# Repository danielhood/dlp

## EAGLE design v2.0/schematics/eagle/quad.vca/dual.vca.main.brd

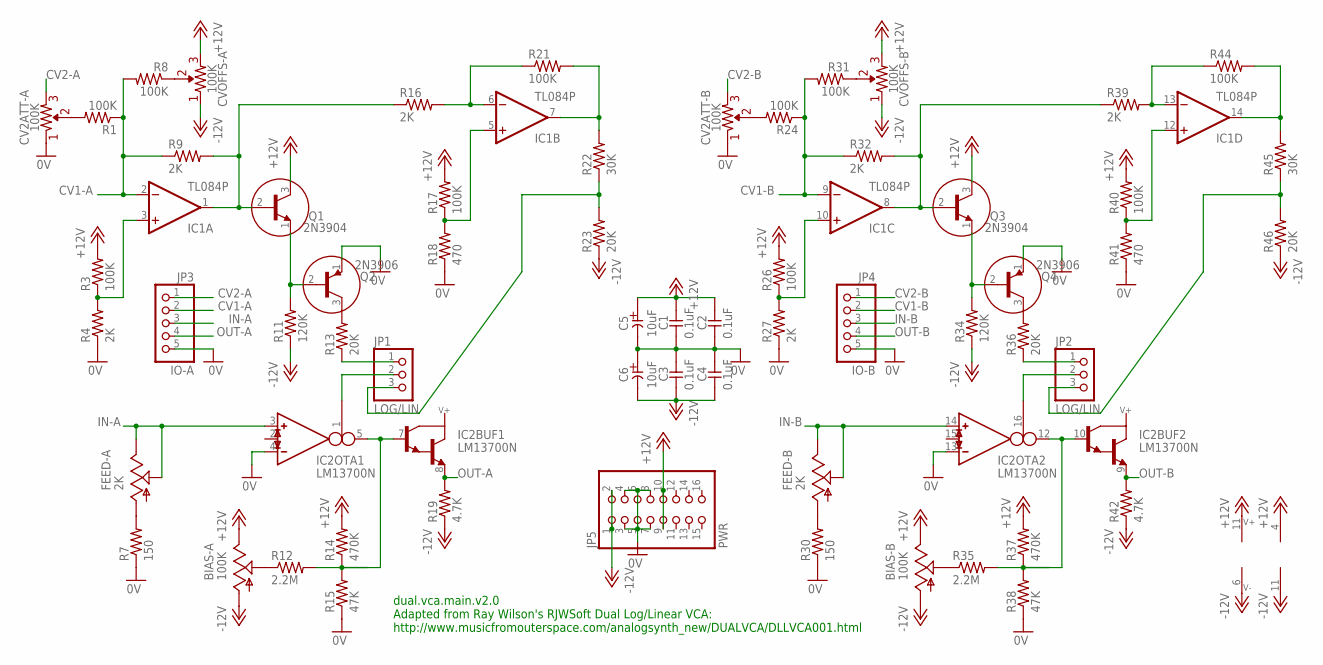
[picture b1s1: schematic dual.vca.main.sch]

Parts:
BIAS-A: 100K; PT-10S
BIAS-B: 100K; PT-10S
C1, C2, C3, C4: 0.1uF; C025-024X044
C5, C6: 10uF; E2-5
CV2ATT-A, CV2ATT-B: 100K; R-VAR
CVOFFS-A: 100K; R-VAR
CVOFFS-B: 100K; R-VAR
FEED-A: 2K; PT-10S
FEED-B: 2K; PT-10S
IC1: TL084P; DIL14
IC2: LM13700N; DIL16
JP1, JP2: LOG/LIN; 1X03
JP3: IO-A; 1X05
JP4: IO-B; 1X05
JP5: PWR; 2X08
Q1, Q3: 2N3904; TO92
Q2, Q4: 2N3906; TO92
R1, R3, R8, R17, R21, R24, R26, R31, R40, R44: 100K; 0207/7
R4, R9, R16, R27, R32, R39: 2K; 0207/7
R7, R30: 150; 0207/7
R11, R34: 120K; 0207/7
R12, R35: 2.2M; 0207/7
R13, R23, R36, R46: 20K; 0207/7
R14, R37: 470K; 0207/7
R15, R38: 47K; 0207/7
R18, R41: 470; 0207/7
R19, R42: 4.7K; 0207/7
R22, R45: 30K; 0207/7

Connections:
0V: C1.2, C2.2, C3.1, C4.1, C5.-, C6.+, CV2ATT-A.R1 (1), CV2ATT-B.R1 (1), IC2.4 (IN_N), IC2.13 (IN_N), JP3.5, JP4.5, JP5.3, JP5.4, JP5.5, JP5.6, JP5.7, JP5.8, Q2.1 (E), Q4.1 (E), R4.1, R7.1, R15.1, R18.1, R27.1, R30.1, R38.1, R41.1
+12V: BIAS-A.E, BIAS-B.E, C1.1, C2.1, C5.+, CVOFFS-A.R2 (2), CVOFFS-B.R2 (2), IC1.4 (V+), IC2.11 (V+), JP5.9, JP5.10, Q1.3 (C), Q3.3 (C), R3.2, R14.2, R17.2, R26.2, R37.2, R40.2
-12V: BIAS-A.A, BIAS-B.A, C3.2, C4.2, C6.-, CVOFFS-A.R1 (1), CVOFFS-B.R1 (1), IC1.11 (V-), IC2.6 (V-), JP5.1, JP5.2, R11.1, R19.1, R23.1, R34.1, R42.1, R46.1
CV1-A: IC1.2 (-IN), JP3.2, R1.1, R8.2, R9.1
CV1-B: IC1.9 (-IN), JP4.2, R24.1, R31.2, R32.1
CV2-A: CV2ATT-A.R2 (2), JP3.1
CV2-B: CV2ATT-B.R2 (2), JP4.1
IN-A: FEED-A.E, FEED-A.S, IC2.3 (IN_P), JP3.3
IN-B: FEED-B.E, FEED-B.S, IC2.14 (IN_P), JP4.3
unnamed: Q2.3 (C), R13.2
unnamed: Q4.3 (C), R36.2
unnamed: IC1.3 (+IN), R3.1, R4.2
unnamed: CVOFFS-A.VAR, R8.1
unnamed: IC1.1 (OUT), Q1.2 (B), R9.2, R16.1
unnamed: Q1.1 (E), Q2.2 (B), R11.2
unnamed: FEED-A.A, R7.2
unnamed: JP1.1, R13.1
unnamed: BIAS-A.S, R12.1
unnamed: IC2.5 (OUT), IC2.7 (B), R12.2, R14.1, R15.2
unnamed: CV2ATT-A.VAR, R1.2
unnamed: JP1.3, R22.1, R23.2
unnamed: IC1.5 (+IN), R17.1, R18.2
unnamed: IC1.6 (-IN), R16.2, R21.1
unnamed: IC2.1 (I_BIAS), JP1.2
unnamed: IC1.7 (OUT), R21.2, R22.2
unnamed: IC1.10 (+IN), R26.1, R27.2
unnamed: CVOFFS-B.VAR, R31.1
unnamed: IC1.8 (OUT), Q3.2 (B), R32.2, R39.1
unnamed: Q3.1 (E), Q4.2 (B), R34.2
unnamed: FEED-B.A, R30.2
unnamed: BIAS-B.S, R35.1
unnamed: IC2.10 (B), IC2.12 (OUT), R35.2, R37.1, R38.2
unnamed: CV2ATT-B.VAR, R24.2
unnamed: IC1.12 (+IN), R40.1, R41.2
unnamed: IC1.13 (-IN), R39.2, R44.1
unnamed: IC1.14 (OUT), R44.2, R45.2
unnamed: JP2.1, R36.1
unnamed: JP2.3, R45.1, R46.2
unnamed: IC2.16 (I_BIAS), JP2.2
OUT-A: IC2.8 (E), JP3.4, R19.2
OUT-B: IC2.9 (E), JP4.4, R42.2

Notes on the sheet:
dual.vca.main.v2.0 Adapted from Ray Wilson's RJWSoft Dual Log/Linear VCA: http://www.musicfromouterspace.com/analogsynth_new/DUALVCA/DLLVCA001.html

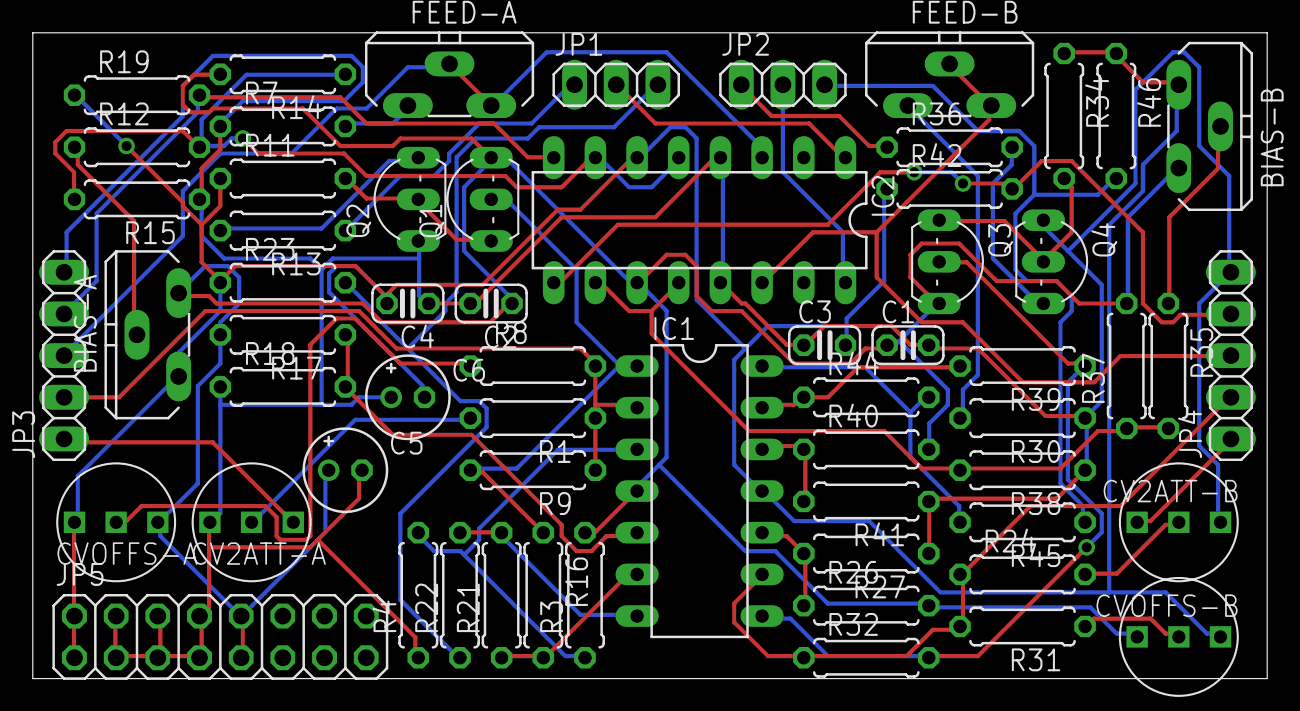
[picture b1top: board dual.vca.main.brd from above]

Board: 2 copper layers, 75.2 x 39.4 mm, 61 parts (0 on the bottom side), 41 nets.

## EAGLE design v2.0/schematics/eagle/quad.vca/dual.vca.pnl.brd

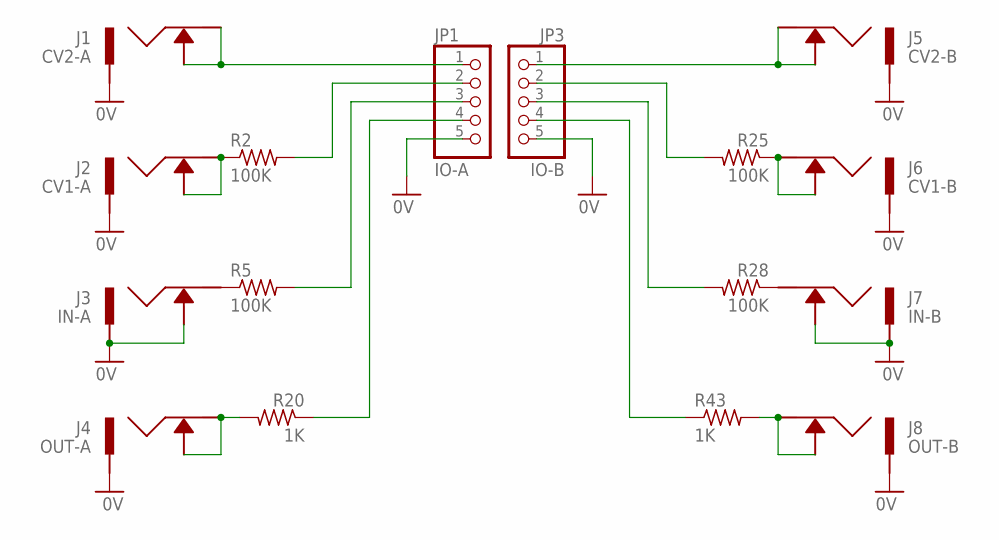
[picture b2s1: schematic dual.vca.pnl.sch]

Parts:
J1: CV2-A; ACJM-MV35-2S
J2: CV1-A; ACJM-MV35-2S
J3: IN-A; ACJM-MV35-2S
J4: OUT-A; ACJM-MV35-2S
J5: CV2-B; ACJM-MV35-2S
J6: CV1-B; ACJM-MV35-2S
J7: IN-B; ACJM-MV35-2S
J8: OUT-B; ACJM-MV35-2S
JP1: IO-A; 1X05
JP3: IO-B; 1X05
R2, R5, R25, R28: 100K; 0207/7
R20, R43: 1K; 0207/7

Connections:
0V: J1.P$1, J2.P$1, J3.P$1, J3.P$2, J4.P$1, J5.P$1, J6.P$1, J7.P$1, J7.P$2, J8.P$1, JP1.5, JP3.5
unnamed: J2.P$2, J2.P$3, R2.1
unnamed: J4.P$2, J4.P$3, R20.2
unnamed: JP1.2, R2.2
unnamed: JP1.3, R5.2
unnamed: JP1.4, R20.1
unnamed: JP3.2, R25.2
unnamed: JP3.3, R28.2
unnamed: JP3.4, R43.1
unnamed: J3.P$3, R5.1
unnamed: J1.P$2, J1.P$3, JP1.1
unnamed: J6.P$2, J6.P$3, R25.1
unnamed: J8.P$2, J8.P$3, R43.2
unnamed: J7.P$3, R28.1
unnamed: J5.P$2, J5.P$3, JP3.1

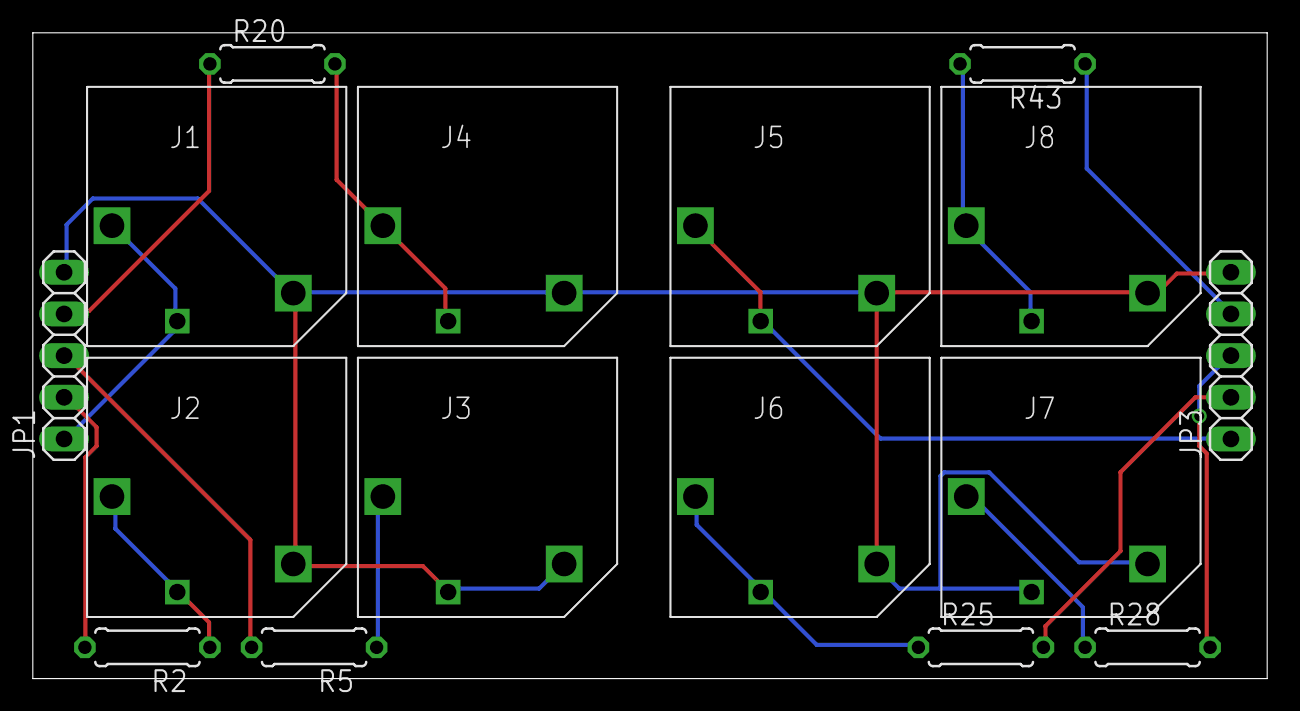
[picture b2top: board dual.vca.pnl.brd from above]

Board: 2 copper layers, 75.2 x 39.4 mm, 16 parts (0 on the bottom side), 15 nets.

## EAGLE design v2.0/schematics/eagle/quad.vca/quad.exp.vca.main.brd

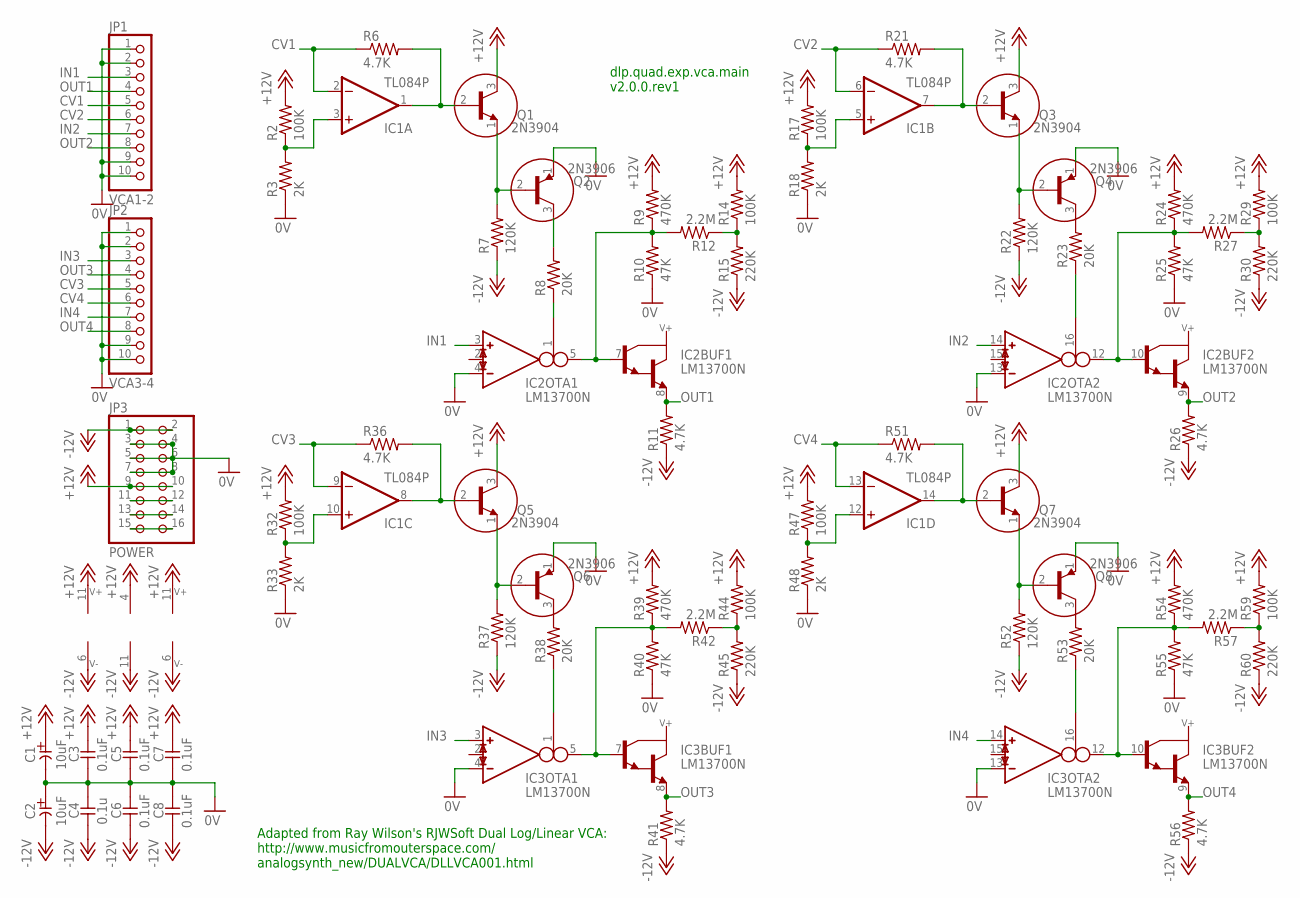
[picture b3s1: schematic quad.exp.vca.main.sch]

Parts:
C1, C2: 10uF; E2-5
C3, C5, C6, C7, C8: 0.1uF; C025-024X044
C4: 0.1u; C025-024X044
IC1: TL084P; DIL14
IC2, IC3: LM13700N; DIL16
JP1: VCA1-2; 1X10
JP2: VCA3-4; 1X10
JP3: POWER; 2X08
Q1, Q3, Q5, Q7: 2N3904; TO92
Q2, Q4, Q6, Q8: 2N3906; TO92
R2, R14, R17, R29, R32, R44, R47, R59: 100K; 0207/7
R3, R18, R33, R48: 2K; 0207/7
R6, R11, R21, R26, R36, R41, R51, R56: 4.7K; 0207/7
R7, R22, R37, R52: 120K; 0207/7
R8, R23, R38, R53: 20K; 0207/7
R9, R24, R39, R54: 470K; 0207/7
R10, R25, R40, R55: 47K; 0207/7
R12, R27, R42, R57: 2.2M; 0207/7
R15, R30, R45, R60: 220K; 0207/7

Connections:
0V: C1.-, C2.+, C3.2, C4.1, C5.2, C6.1, C7.2, C8.1, IC2.4 (IN_N), IC2.13 (IN_N), IC3.4 (IN_N), IC3.13 (IN_N), JP1.1, JP1.2, JP1.9, JP1.10, JP2.1, JP2.2, JP2.9, JP2.10, JP3.3, JP3.4, JP3.5, JP3.6, JP3.7, JP3.8, Q2.1 (E), Q4.1 (E), Q6.1 (E), Q8.1 (E), R3.1, R10.1, R18.1, R25.1, R33.1, R40.1, R48.1, R55.1
+12V: C1.+, C3.1, C5.1, C7.1, IC1.4 (V+), IC2.11 (V+), IC3.11 (V+), JP3.9, JP3.10, Q1.3 (C), Q3.3 (C), Q5.3 (C), Q7.3 (C), R2.2, R9.2, R14.2, R17.2, R24.2, R29.2, R32.2, R39.2, R44.2, R47.2, R54.2, R59.2
-12V: C2.-, C4.2, C6.2, C8.2, IC1.11 (V-), IC2.6 (V-), IC3.6 (V-), JP3.1, JP3.2, R7.1, R11.1, R15.1, R22.1, R26.1, R30.1, R37.1, R41.1, R45.1, R52.1, R56.1, R60.1
CV1: IC1.2 (-IN), JP1.5, R6.1
CV2: IC1.6 (-IN), JP1.6, R21.1
CV3: IC1.9 (-IN), JP2.5, R36.1
CV4: IC1.13 (-IN), JP2.6, R51.1
IN1: IC2.3 (IN_P), JP1.3
IN2: IC2.14 (IN_P), JP1.7
IN3: IC3.3 (IN_P), JP2.3
IN4: IC3.14 (IN_P), JP2.7
unnamed: IC1.3 (+IN), R2.1, R3.2
unnamed: IC1.10 (+IN), R32.1, R33.2
unnamed: IC1.1 (OUT), Q1.2 (B), R6.2
unnamed: Q1.1 (E), Q2.2 (B), R7.2
unnamed: Q2.3 (C), R8.2
unnamed: IC1.8 (OUT), Q5.2 (B), R36.2
unnamed: Q5.1 (E), Q6.2 (B), R37.2
unnamed: IC2.5 (OUT), IC2.7 (B), R9.1, R10.2, R12.2
unnamed: Q4.3 (C), R23.2
unnamed: IC3.5 (OUT), IC3.7 (B), R39.1, R40.2, R42.2
unnamed: IC2.1 (I_BIAS), R8.1
unnamed: IC1.5 (+IN), R17.1, R18.2
unnamed: IC3.1 (I_BIAS), R38.1
unnamed: IC1.7 (OUT), Q3.2 (B), R21.2
unnamed: Q3.1 (E), Q4.2 (B), R22.2
unnamed: Q8.3 (C), R53.2
unnamed: IC1.12 (+IN), R47.1, R48.2
unnamed: IC2.10 (B), IC2.12 (OUT), R24.1, R25.2, R27.2
unnamed: IC1.14 (OUT), Q7.2 (B), R51.2
unnamed: Q7.1 (E), Q8.2 (B), R52.2
unnamed: Q6.3 (C), R38.2
unnamed: IC2.16 (I_BIAS), R23.1
unnamed: IC3.10 (B), IC3.12 (OUT), R54.1, R55.2, R57.2
unnamed: IC3.16 (I_BIAS), R53.1
unnamed: R12.1, R14.1, R15.2
unnamed: R27.1, R29.1, R30.2
unnamed: R42.1, R44.1, R45.2
unnamed: R57.1, R59.1, R60.2
unnamed: JP3.11, JP3.12
unnamed: JP3.13, JP3.14
unnamed: JP3.15, JP3.16
OUT1: IC2.8 (E), JP1.4, R11.2
OUT2: IC2.9 (E), JP1.8, R26.2
OUT3: IC3.8 (E), JP2.4, R41.2
OUT4: IC3.9 (E), JP2.8, R56.2

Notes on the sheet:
Adapted from Ray Wilson's RJWSoft Dual Log/Linear VCA: http://www.musicfromouterspace.com/ analogsynth_new/DUALVCA/DLLVCA001.html
dlp.quad.exp.vca.main v2.0.0.rev1

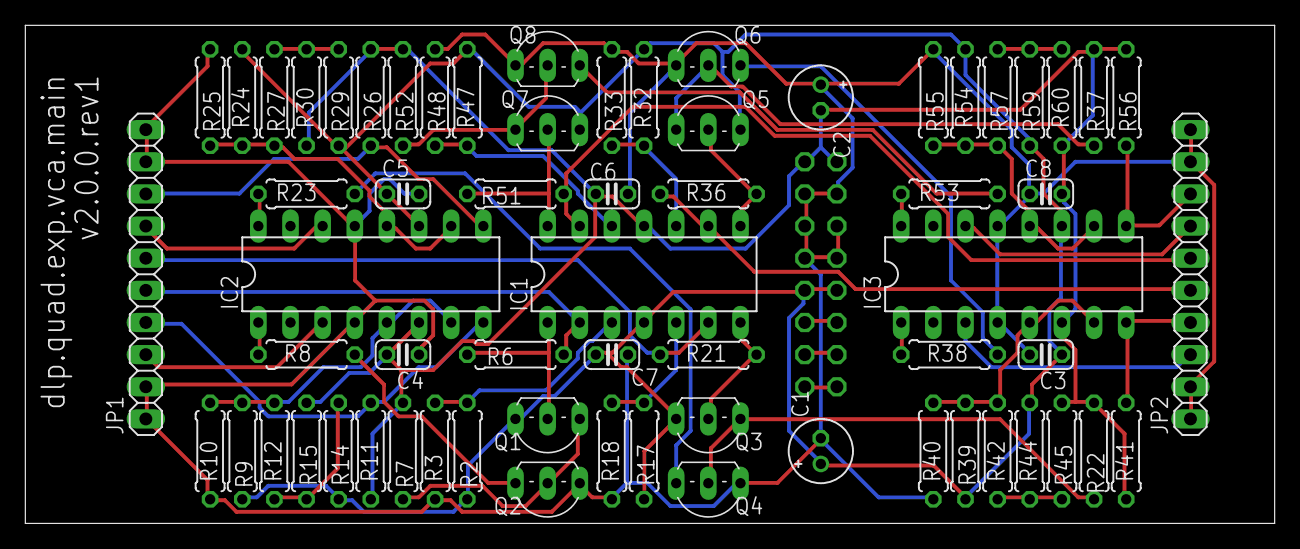
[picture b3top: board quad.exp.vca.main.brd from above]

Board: 2 copper layers, 98.7 x 39.4 mm, 66 parts (1 on the bottom side), 46 nets.

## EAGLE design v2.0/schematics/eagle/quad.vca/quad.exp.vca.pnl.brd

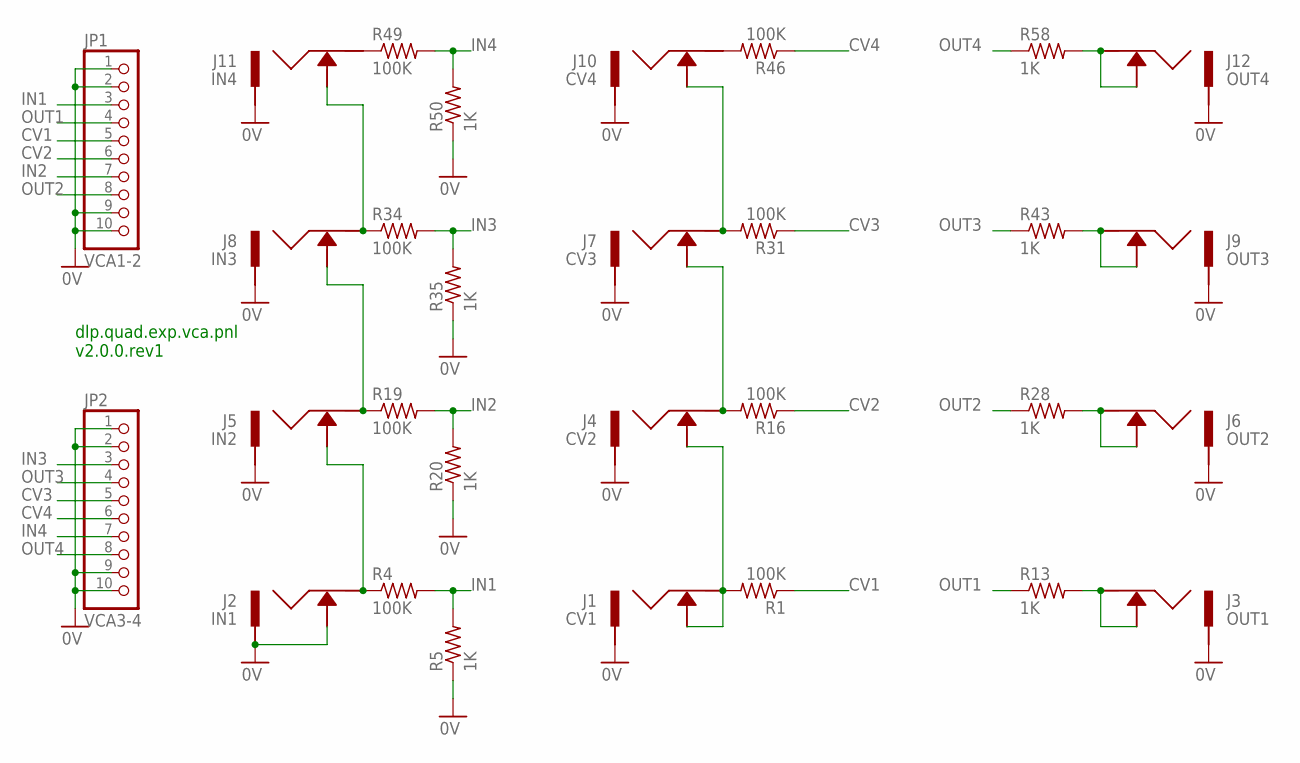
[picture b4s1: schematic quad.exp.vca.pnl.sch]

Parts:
J1: CV1; ACJM-MV35-2S
J2: IN1; ACJM-MV35-2S
J3: OUT1; ACJM-MV35-2S
J4: CV2; ACJM-MV35-2S
J5: IN2; ACJM-MV35-2S
J6: OUT2; ACJM-MV35-2S
J7: CV3; ACJM-MV35-2S
J8: IN3; ACJM-MV35-2S
J9: OUT3; ACJM-MV35-2S
J10: CV4; ACJM-MV35-2S
J11: IN4; ACJM-MV35-2S
J12: OUT4; ACJM-MV35-2S
JP1: VCA1-2; 1X10
JP2: VCA3-4; 1X10
R1, R4, R16, R19, R31, R34, R46, R49: 100K; 0207/7
R5, R13, R20, R28, R35, R43, R50, R58: 1K; 0207/7

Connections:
0V: J1.P$1, J2.P$1, J2.P$2, J3.P$1, J4.P$1, J5.P$1, J6.P$1, J7.P$1, J8.P$1, J9.P$1, J10.P$1, J11.P$1, J12.P$1, JP1.1, JP1.2, JP1.9, JP1.10, JP2.1, JP2.2, JP2.9, JP2.10, R5.1, R20.1, R35.1, R50.1
CV1: JP1.5, R1.1
CV2: JP1.6, R16.1
CV3: JP2.5, R31.1
CV4: JP2.6, R46.1
IN1: JP1.3, R4.2, R5.2
IN2: JP1.7, R19.2, R20.2
IN3: JP2.3, R34.2, R35.2
IN4: JP2.7, R49.2, R50.2
unnamed: J9.P$2, J9.P$3, R43.2
unnamed: J3.P$2, J3.P$3, R13.2
unnamed: J2.P$3, J5.P$2, R4.1
unnamed: J5.P$3, J8.P$2, R19.1
unnamed: J8.P$3, J11.P$2, R34.1
unnamed: J10.P$3, R46.2
unnamed: J7.P$3, J10.P$2, R31.2
unnamed: J4.P$3, J7.P$2, R16.2
unnamed: J1.P$2, J1.P$3, J4.P$2, R1.2
unnamed: J6.P$2, J6.P$3, R28.2
unnamed: J12.P$2, J12.P$3, R58.2
unnamed: J11.P$3, R49.1
OUT1: JP1.4, R13.1
OUT2: JP1.8, R28.1
OUT3: JP2.4, R43.1
OUT4: JP2.8, R58.1

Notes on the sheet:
dlp.quad.exp.vca.pnl v2.0.0.rev1

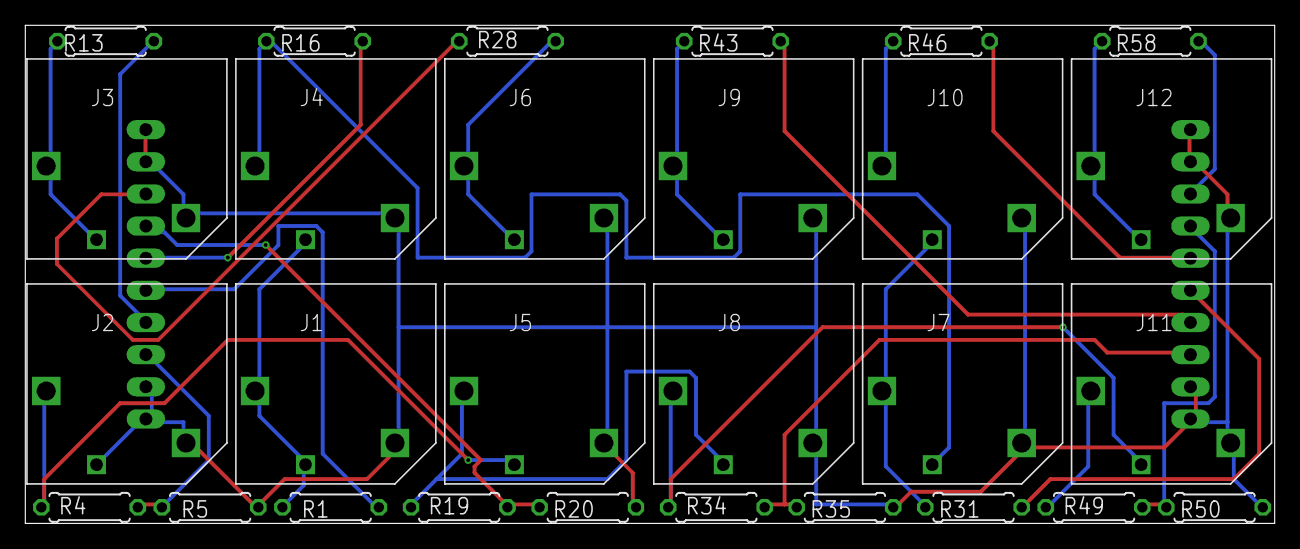
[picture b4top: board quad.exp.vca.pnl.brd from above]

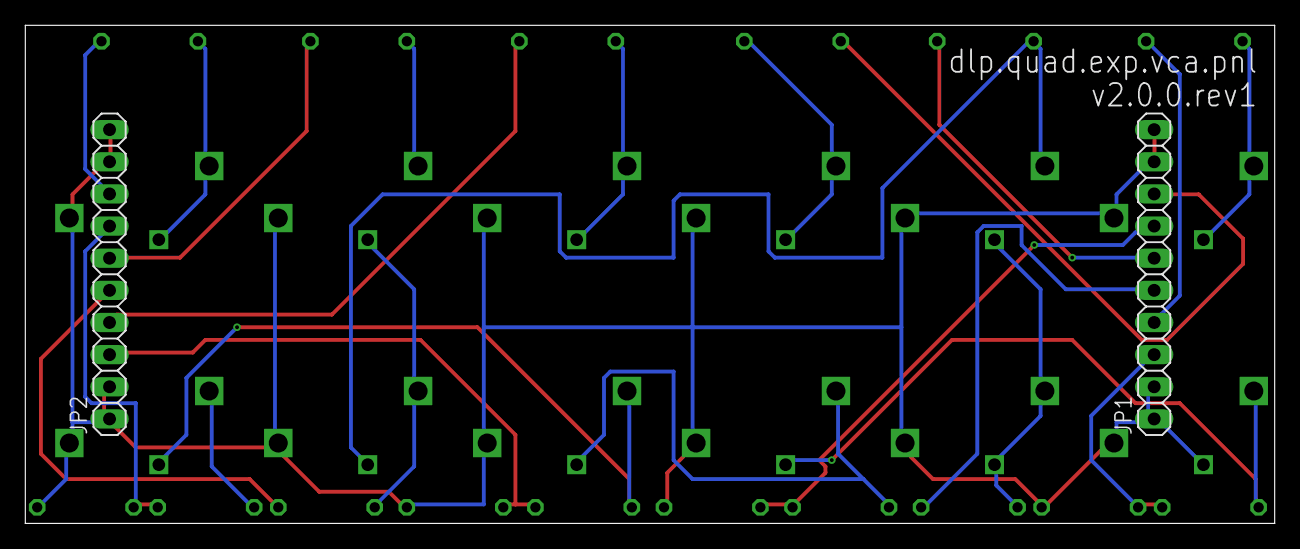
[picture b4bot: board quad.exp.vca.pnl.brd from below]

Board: 2 copper layers, 98.7 x 39.4 mm, 30 parts (2 on the bottom side), 25 nets.

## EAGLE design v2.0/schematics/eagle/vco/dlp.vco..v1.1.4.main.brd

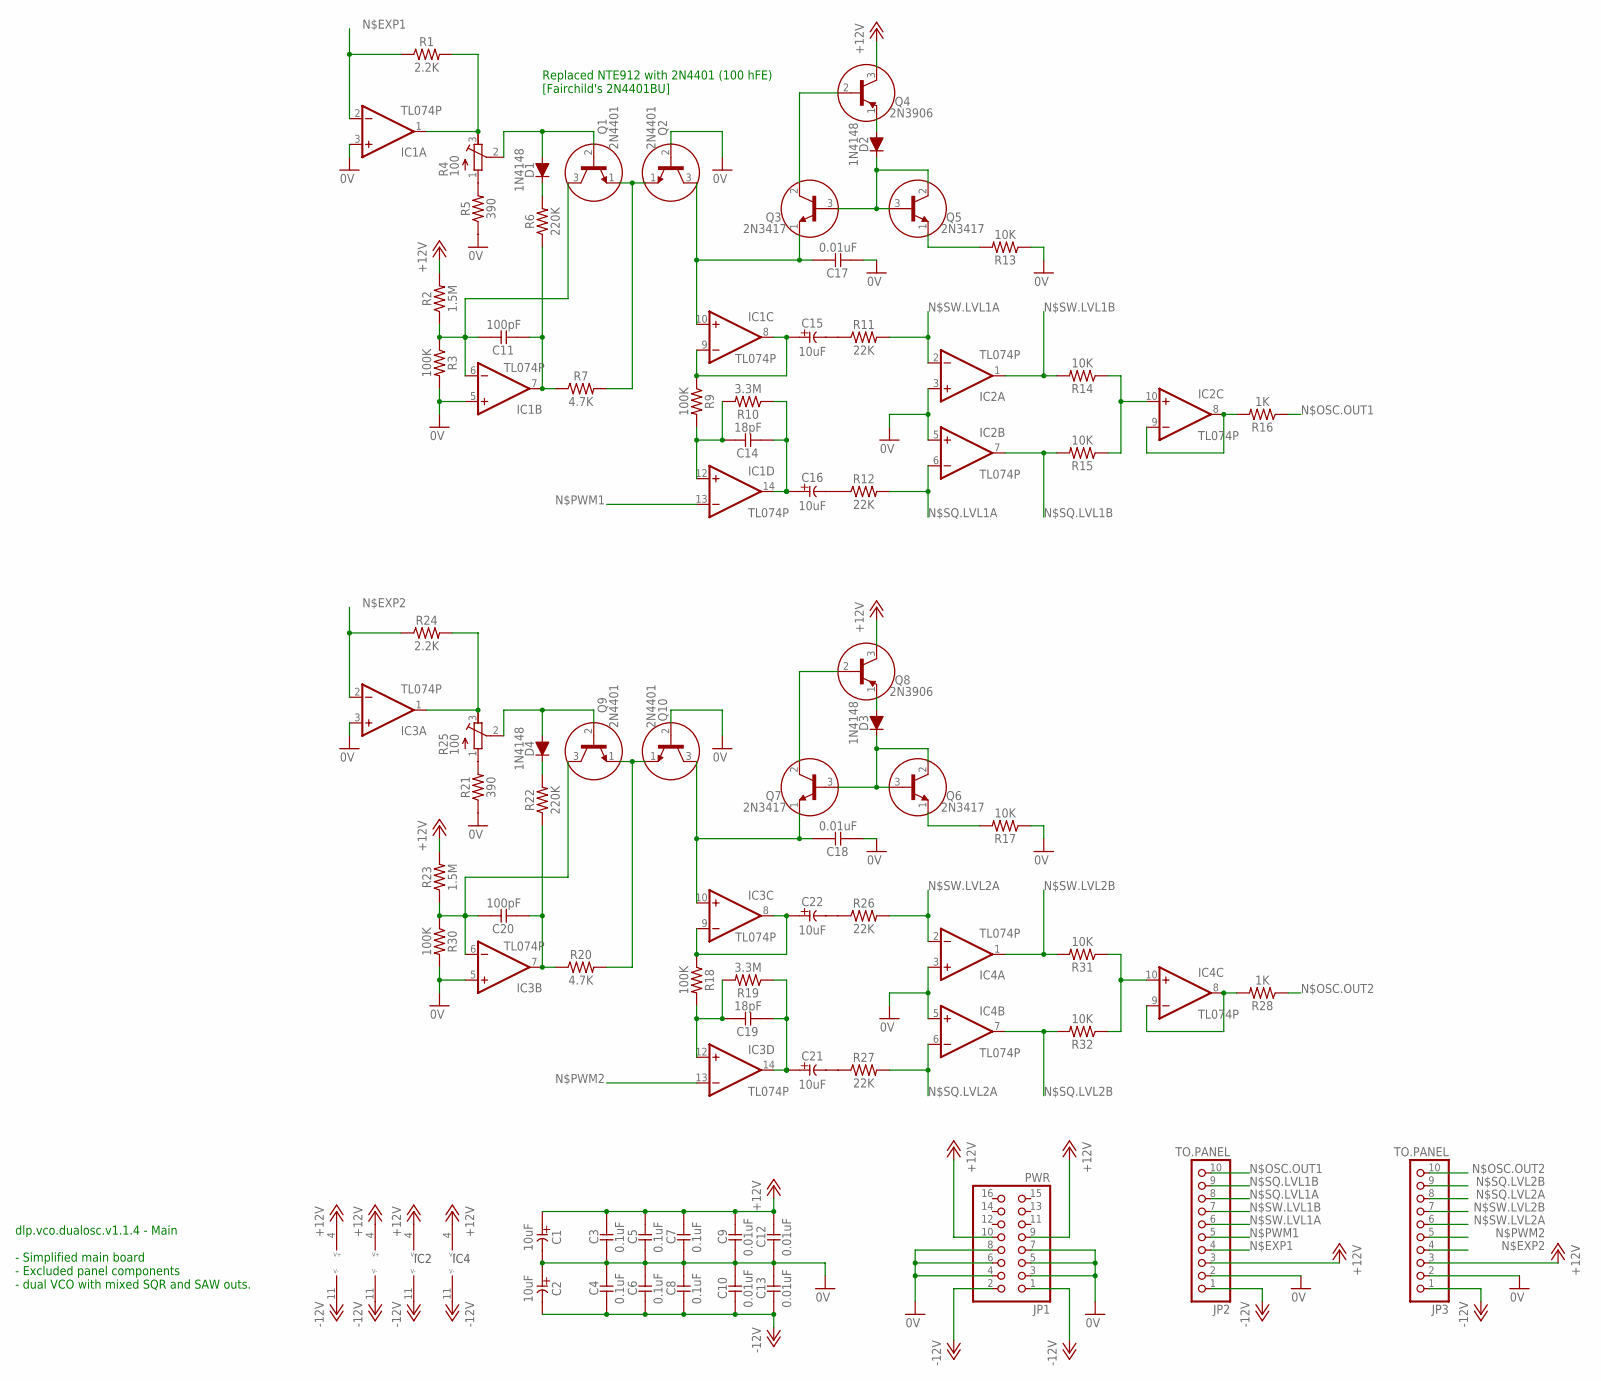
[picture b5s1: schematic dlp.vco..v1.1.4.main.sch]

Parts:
C1, C2, C15, C16, C21, C22: 10uF; E2-5
C3, C4, C5, C6, C7, C8: 0.1uF; C025-024X044
C9, C10, C12, C13, C17, C18: 0.01uF; C025-024X044
C11, C20: 100pF; C025-024X044
C14, C19: 18pF; C025-024X044
D1, D2, D3, D4: 1N4148; DO35-7
IC1, IC2, IC3, IC4: TL074P; DIL14
JP1: PWR; 2X08
JP2, JP3: TO.PANEL; 1X10
Q1, Q2, Q9, Q10: 2N4401; TO92
Q3, Q5, Q6, Q7: 2N3417; TO92
Q4, Q8: 2N3906; TO92
R1, R24: 2.2K; 0309/10
R2, R23: 1.5M; 0309/10
R3, R9, R18, R30: 100K; 0309/10
R4, R25: 100; RTRIM3296Y
R5, R21: 390; 0309/10
R6, R22: 220K; 0309/10
R7, R20: 4.7K; 0309/10
R10, R19: 3.3M; 0309/10
R11, R12, R26, R27: 22K; 0309/10
R13, R14, R15, R17, R31, R32: 10K; 0309/10
R16, R28: 1K; 0309/10

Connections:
0V: C1.-, C2.+, C3.2, C4.1, C5.2, C6.1, C7.2, C8.1, C9.2, C10.1, C12.2, C13.1, C17.2, C18.2, IC1.3 (+IN), IC1.5 (+IN), IC2.3 (+IN), IC2.5 (+IN), IC3.3 (+IN), IC3.5 (+IN), IC4.3 (+IN), IC4.5 (+IN), JP1.3, JP1.4, JP1.5, JP1.6, JP1.7, JP1.8, JP2.2, JP3.2, Q2.2 (B), Q10.2 (B), R3.2, R5.1, R13.1, R17.1, R21.1, R30.2
+12V: C1.+, C3.1, C5.1, C7.1, C9.1, C12.1, IC1.4 (V+), IC2.4 (V+), IC3.4 (V+), IC4.4 (V+), JP1.9, JP1.10, JP2.3, JP3.3, Q4.3 (C), Q8.3 (C), R2.2, R23.2
-12V: C2.-, C4.2, C6.2, C8.2, C10.2, C13.2, IC1.11 (V-), IC2.11 (V-), IC3.11 (V-), IC4.11 (V-), JP1.1, JP1.2, JP2.1, JP3.1
unnamed: C17.1, IC1.10 (+IN), Q2.3 (C), Q3.1 (E)
unnamed: Q3.2 (C), Q4.2 (B)
unnamed: D2.A, Q4.1 (E)
unnamed: C15.+, IC1.8 (OUT), IC1.9 (-IN), R9.1
unnamed: D2.C, Q3.3 (B), Q5.2 (C), Q5.3 (B)
unnamed: Q5.1 (E), R13.2
unnamed: C14.1, IC1.12 (+IN), R9.2, R10.2
unnamed: C14.2, C16.+, IC1.14 (OUT), R10.1
unnamed: D1.A, Q1.2 (B), R4.2 (S)
unnamed: C18.1, IC3.10 (+IN), Q7.1 (E), Q10.3 (C)
unnamed: Q1.1 (E), Q2.1 (E), R7.2
unnamed: D1.C, R6.2
unnamed: R4.1 (A), R5.2
unnamed: C11.1, IC1.6 (-IN), Q1.3 (C), R2.1, R3.1
unnamed: IC1.1 (OUT), R1.2, R4.3 (E)
unnamed: D3.A, Q8.1 (E)
unnamed: IC2.10 (+IN), R14.1, R15.1
unnamed: Q6.1 (E), R17.2
unnamed: IC2.8 (OUT), IC2.9 (-IN), R16.2
unnamed: D3.C, Q6.2 (C), Q6.3 (B), Q7.3 (B)
unnamed: Q7.2 (C), Q8.2 (B)
unnamed: C22.+, IC3.8 (OUT), IC3.9 (-IN), R18.1
unnamed: C19.1, IC3.12 (+IN), R18.2, R19.2
unnamed: C19.2, C21.+, IC3.14 (OUT), R19.1
unnamed: Q9.1 (E), Q10.1 (E), R20.2
unnamed: D4.C, R22.2
unnamed: C15.-, R11.1
unnamed: C16.-, R12.1
unnamed: C20.1, IC3.6 (-IN), Q9.3 (C), R23.1, R30.1
unnamed: IC3.1 (OUT), R24.2, R25.3 (E)
unnamed: C22.-, R26.1
unnamed: C21.-, R27.1
unnamed: IC4.10 (+IN), R31.1, R32.1
unnamed: IC4.8 (OUT), IC4.9 (-IN), R28.2
unnamed: C11.2, IC1.7 (OUT), R6.1, R7.1
unnamed: R21.2, R25.1 (A)
unnamed: C20.2, IC3.7 (OUT), R20.1, R22.1
unnamed: D4.A, Q9.2 (B), R25.2 (S)
N$EXP1: IC1.2 (-IN), JP2.4, R1.1
N$EXP2: IC3.2 (-IN), JP3.4, R24.1
N$OSC.OUT1: JP2.10, R16.1
N$OSC.OUT2: JP3.10, R28.1
N$PWM1: JP2.5
N$PWM2: JP3.5
N$SQ.LVL1A: IC2.6 (-IN), JP2.8, R12.2
N$SQ.LVL1B: IC2.7 (OUT), JP2.9, R15.2
N$SQ.LVL2A: IC4.6 (-IN), JP3.8, R27.2
N$SQ.LVL2B: IC4.7 (OUT), JP3.9, R32.2
N$SW.LVL1A: IC2.2 (-IN), JP2.6, R11.2
N$SW.LVL1B: IC2.1 (OUT), JP2.7, R14.2
N$SW.LVL2A: IC4.2 (-IN), JP3.6, R26.2
N$SW.LVL2B: IC4.1 (OUT), JP3.7, R31.2

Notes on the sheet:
IC2
IC4
dlp.vco.dualosc.v1.1.4 - Main - Simplified main board - Excluded panel components - dual VCO with mixed SQR and SAW outs.
Replaced NTE912 with 2N4401 (100 hFE) [Fairchild's 2N4401BU]

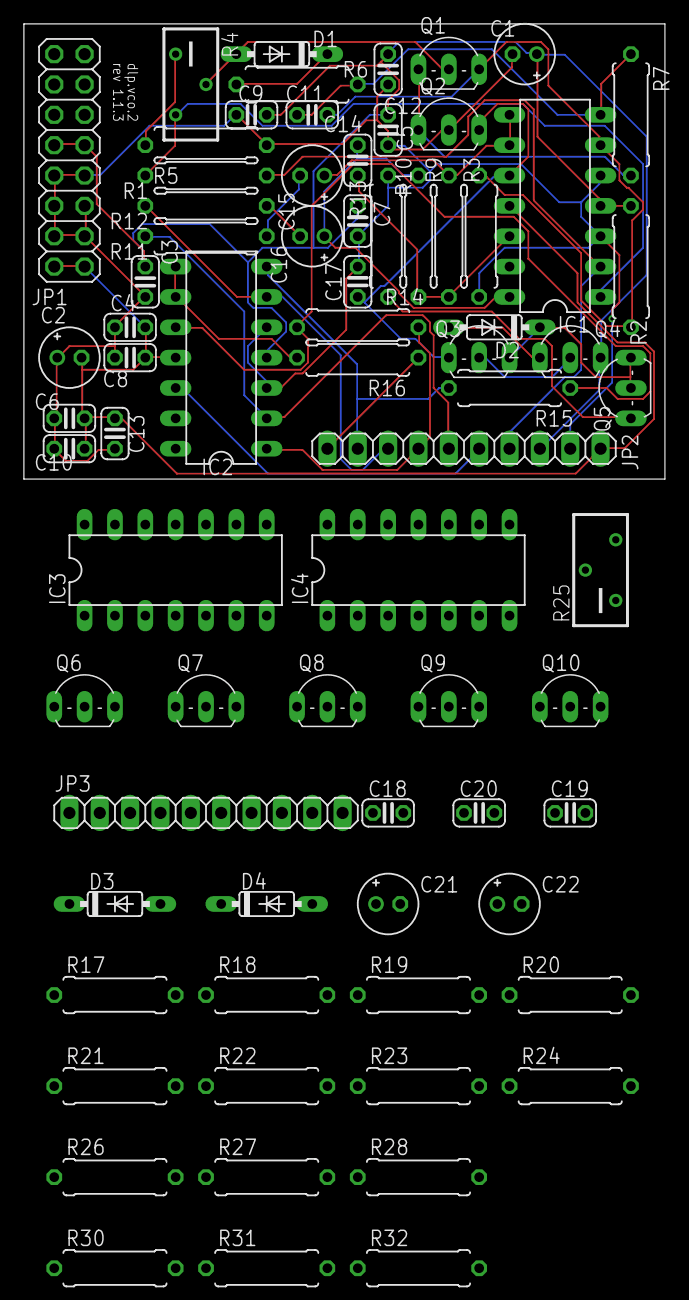
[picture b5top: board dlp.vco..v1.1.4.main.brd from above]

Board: 2 copper layers, 53.6 x 38.1 mm, 73 parts (0 on the bottom side), 53 nets.

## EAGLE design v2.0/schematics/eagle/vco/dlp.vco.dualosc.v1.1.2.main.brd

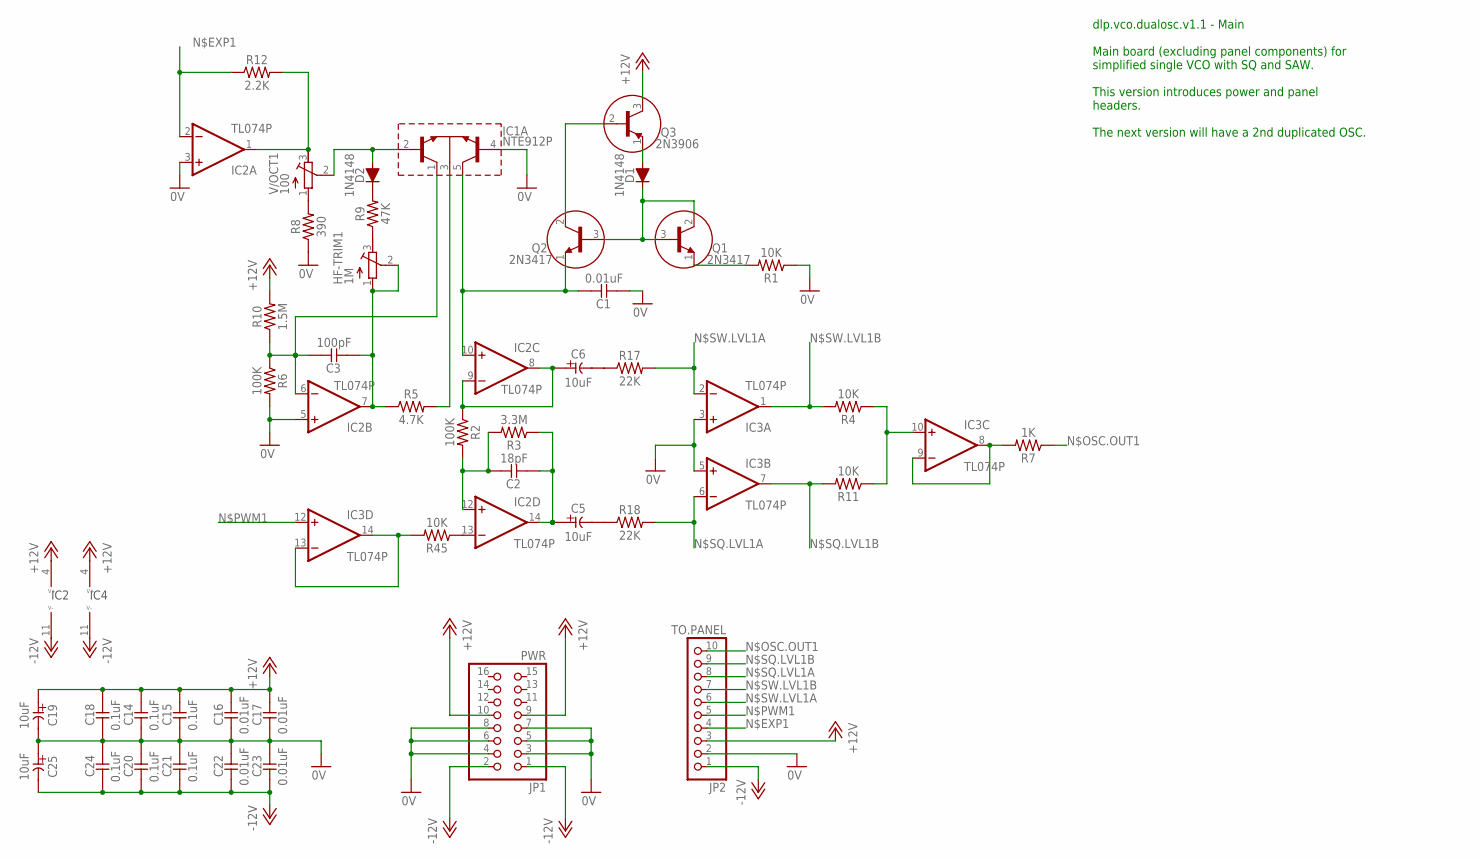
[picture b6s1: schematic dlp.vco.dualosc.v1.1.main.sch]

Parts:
C1, C16, C17, C22, C23: 0.01uF; C025-024X044
C2: 18pF; C025-024X044
C3: 100pF; C025-024X044
C5, C6, C19, C25: 10uF; E2-5
C14, C15, C18, C20, C21, C24: 0.1uF; C025-024X044
D1, D2: 1N4148; DO35-7
HF-TRIM1: 1M; RTRIM3296Y
IC1: NTE912P; DIL14
IC2, IC3: TL074P; DIL14
JP1: PWR; 2X08
JP2: TO.PANEL; 1X10
Q1, Q2: 2N3417; TO92
Q3: 2N3906; TO92
R1, R4, R11, R45: 10K; 0309/10
R2, R6: 100K; 0309/10
R3: 3.3M; 0309/10
R5: 4.7K; 0309/10
R7: 1K; 0309/10
R8: 390; 0309/10
R9: 47K; 0309/10
R10: 1.5M; 0309/10
R12: 2.2K; 0309/10
R17, R18: 22K; 0309/10
V/OCT1: 100; RTRIM3296Y

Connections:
0V: C1.2, C14.2, C15.2, C16.2, C17.2, C18.2, C19.-, C20.1, C21.1, C22.1, C23.1, C24.1, C25.+, IC1.4 (B3), IC2.3 (+IN), IC2.5 (+IN), IC3.3 (+IN), IC3.5 (+IN), JP1.3, JP1.4, JP1.5, JP1.6, JP1.7, JP1.8, JP2.2, R1.1, R6.2, R8.1; also elsewhere on the board
+12V: C14.1, C15.1, C16.1, C17.1, C18.1, C19.+, IC2.4 (V+), IC3.4 (V+), JP1.9, JP1.10, JP2.3, Q3.3 (C), R10.2
-12V: C20.2, C21.2, C22.2, C23.2, C24.2, C25.-, IC2.11 (V-), IC3.11 (V-), JP1.1, JP1.2, JP2.1
unnamed 3: C1.1, IC1.5 (C3), IC2.10 (+IN), Q2.1 (E); also elsewhere on the board
unnamed: Q2.2 (C), Q3.2 (B)
unnamed: D1.A, Q3.1 (E)
unnamed: C6.+, IC2.8 (OUT), IC2.9 (-IN), R2.1
unnamed: D1.C, Q1.2 (C), Q1.3 (B), Q2.3 (B)
unnamed: Q1.1 (E), R1.2
unnamed: C2.1, IC2.12 (+IN), R2.2, R3.2
unnamed: IC2.13 (-IN), R45.1
unnamed: C2.2, C5.+, IC2.14 (OUT), R3.1
unnamed 12: D2.A, IC1.2 (B1), V/OCT1.2 (S); also elsewhere on the board
unnamed 13: IC1.3 (E), R5.2; also elsewhere on the board
unnamed: D2.C, R9.2
unnamed: R8.2, V/OCT1.1 (A)
unnamed 16: C3.1, IC1.1 (C1), IC2.6 (-IN), R6.1, R10.1; also elsewhere on the board
unnamed: IC2.1 (OUT), R12.2, V/OCT1.3 (E)
unnamed: IC3.10 (+IN), R4.1, R11.1
unnamed: IC3.8 (OUT), IC3.9 (-IN), R7.2
unnamed: IC3.13 (-IN), IC3.14 (OUT), R45.2
unnamed: C6.-, R17.1
unnamed: C5.-, R18.1
N$EXP1: IC2.2 (-IN), JP2.4, R12.1
N$OSC.OUT1: JP2.10, R7.1
N$PWM1: IC3.12 (+IN), JP2.5
N$SQ.LVL1A: IC3.6 (-IN), JP2.8, R18.2
N$SQ.LVL1B: IC3.7 (OUT), JP2.9, R11.2
N$SW.LVL1A: IC3.2 (-IN), JP2.6, R17.2
N$SW.LVL1B: IC3.1 (OUT), JP2.7, R4.2

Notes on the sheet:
IC2
IC4
dlp.vco.dualosc.v1.1 - Main Main board (excluding panel components) for simplified single VCO with SQ and SAW. This version introduces power and panel headers. The next version will have a 2nd duplicated OSC.
